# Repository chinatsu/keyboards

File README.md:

# keyboards

silly keyboard experiments

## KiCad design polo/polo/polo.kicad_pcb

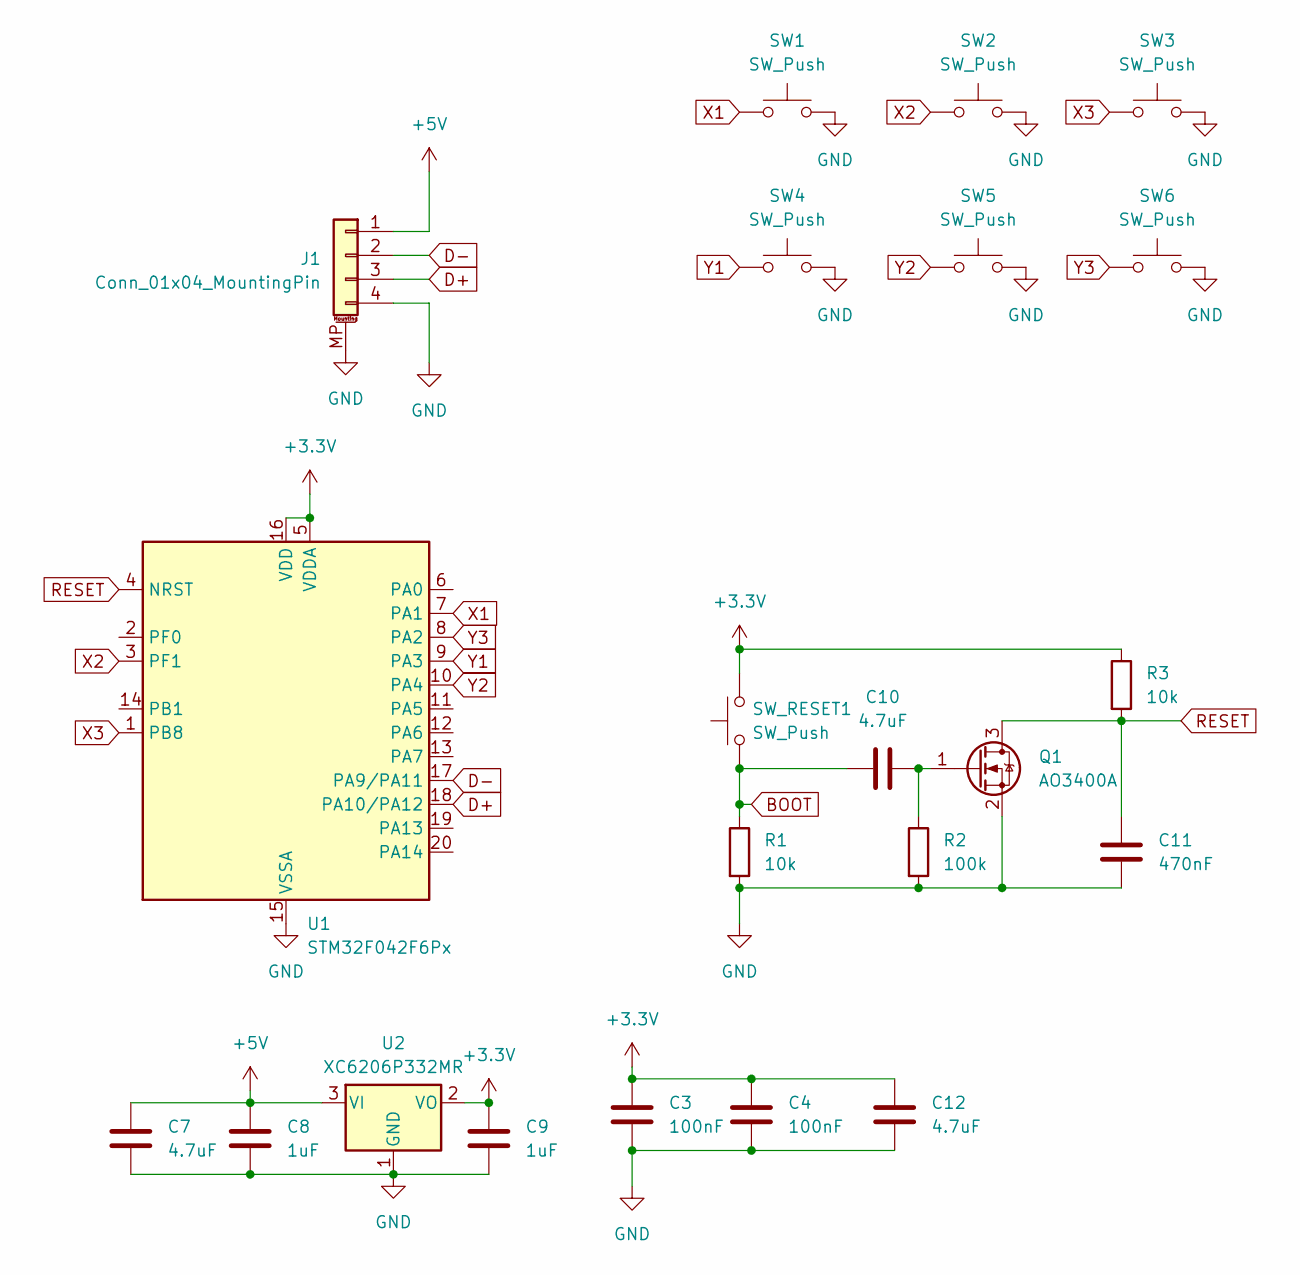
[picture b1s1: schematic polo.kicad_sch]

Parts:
C3, C4: 100nF; C_0805_2012Metric
C7, C10, C12: 4.7uF; C_0805_2012Metric
C8, C9: 1uF; C_0805_2012Metric
C11: 470nF; C_0805_2012Metric
J1: Conn_01x04_MountingPin; JST_SH_SM04B-SRSS-TB_1x04-1MP_P1.00mm_Horizontal
Q1: AO3400A; SOT-23
R1, R3: 10k; R_0805_2012Metric
R2: 100k; R_0805_2012Metric
SW1, SW2, SW3, SW4, SW5, SW6: SW_Push; SW_Cherry_MX_1.00u_PCB
SW_RESET1: SW_Push; SW_PUSH_1P1T_6x3.5mm_H4.3_APEM_MJTP1243
U1: STM32F042F6Px; TSSOP-20_4.4x6.5mm_P0.65mm
U2: XC6206P332MR; SOT-23-3

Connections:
+3.3V: C3.1, C4.1, C9.1, C12.1, R3.1, SW_RESET1.2, U1.5 (VDDA), U1.16 (VDD), U2.2 (VO)
+5V: C7.1, C8.1, J1.1, U2.3 (VI)
BOOT: C10.1, R1.1, SW_RESET1.1
D+: J1.3, U1.18 (PA10/PA12)
D-: J1.2, U1.17 (PA9/PA11)
GND: C3.2, C4.2, C7.2, C8.2, C9.2, C11.2, C12.2, J1.4, J1.MP (MountPin), Q1.2 (S), R1.2, R2.2, SW1.2, SW2.2, SW3.2, SW4.2, SW5.2, SW6.2, U1.15 (VSSA), U2.1 (GND)
unnamed: C10.2, Q1.1 (G), R2.1
RESET: C11.1, Q1.3 (D), R3.2, U1.4 (NRST)
X1: SW1.1, U1.7 (PA1)
X2: SW2.1, U1.3 (PF1)
X3: SW3.1, U1.1 (PB8)
Y1: SW4.1, U1.9 (PA3)
Y2: SW5.1, U1.10 (PA4)
Y3: SW6.1, U1.8 (PA2)

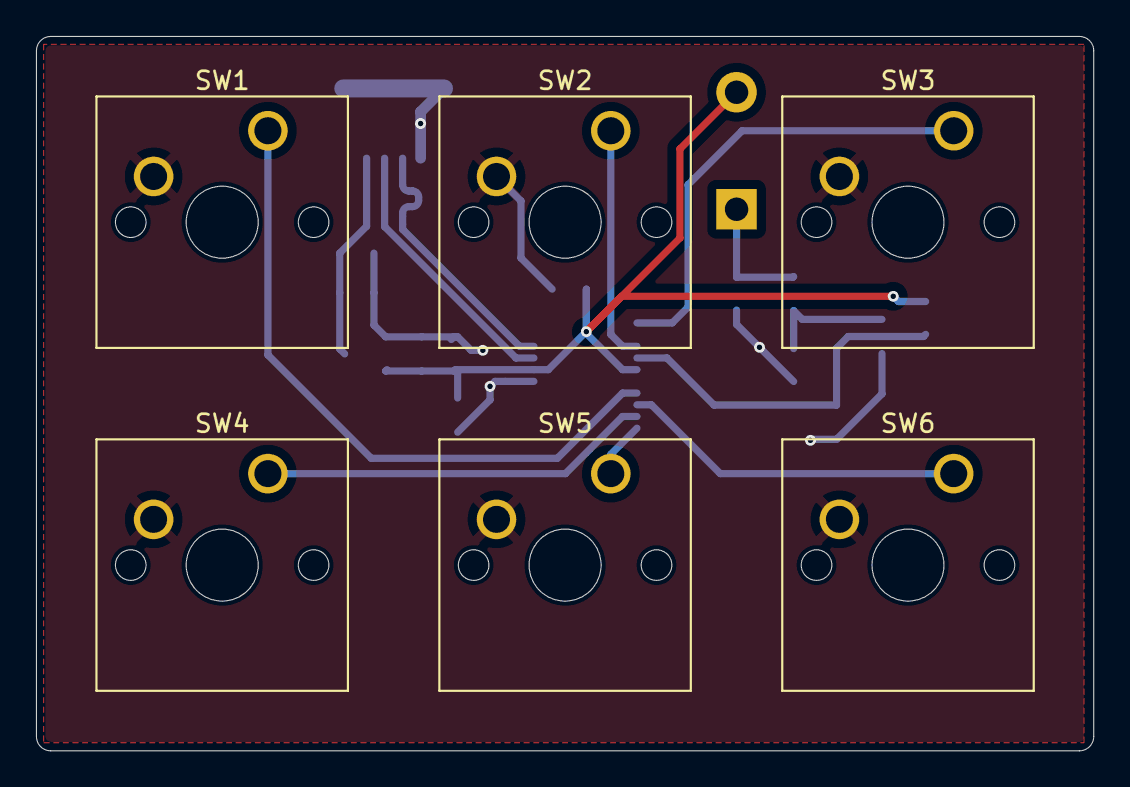
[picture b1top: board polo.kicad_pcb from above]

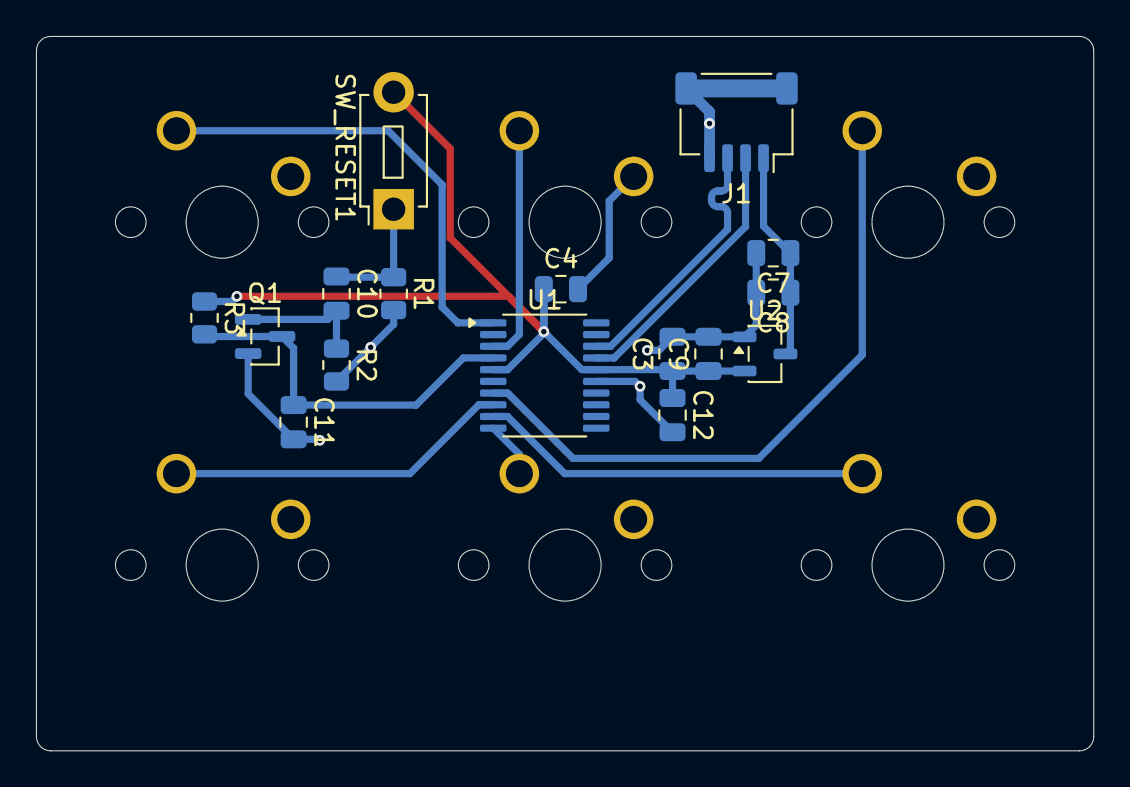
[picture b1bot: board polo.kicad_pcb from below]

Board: 2 copper layers, 58.7 x 39.7 mm, 22 parts (16 on the bottom side), 14 nets.

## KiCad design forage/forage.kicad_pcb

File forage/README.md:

# forage

my first attempt at a keyboard not using a pro micro or similar... let's see how it goes

## features

- 48 keys
- winkeyless
- arrow cluster
- uses unified daughterboard (s1, probably)

## layout

[keyboard-layout-editor](http://www.keyboard-layout-editor.com/#/gists/264eb9b4cfe87a9984ab72605ec59c53)

## plans

- design a case, maybe try to get a gasket mount style going?
- spend way too much money on a prototype cnc'd case
- be sad that things don't work, never work on this again

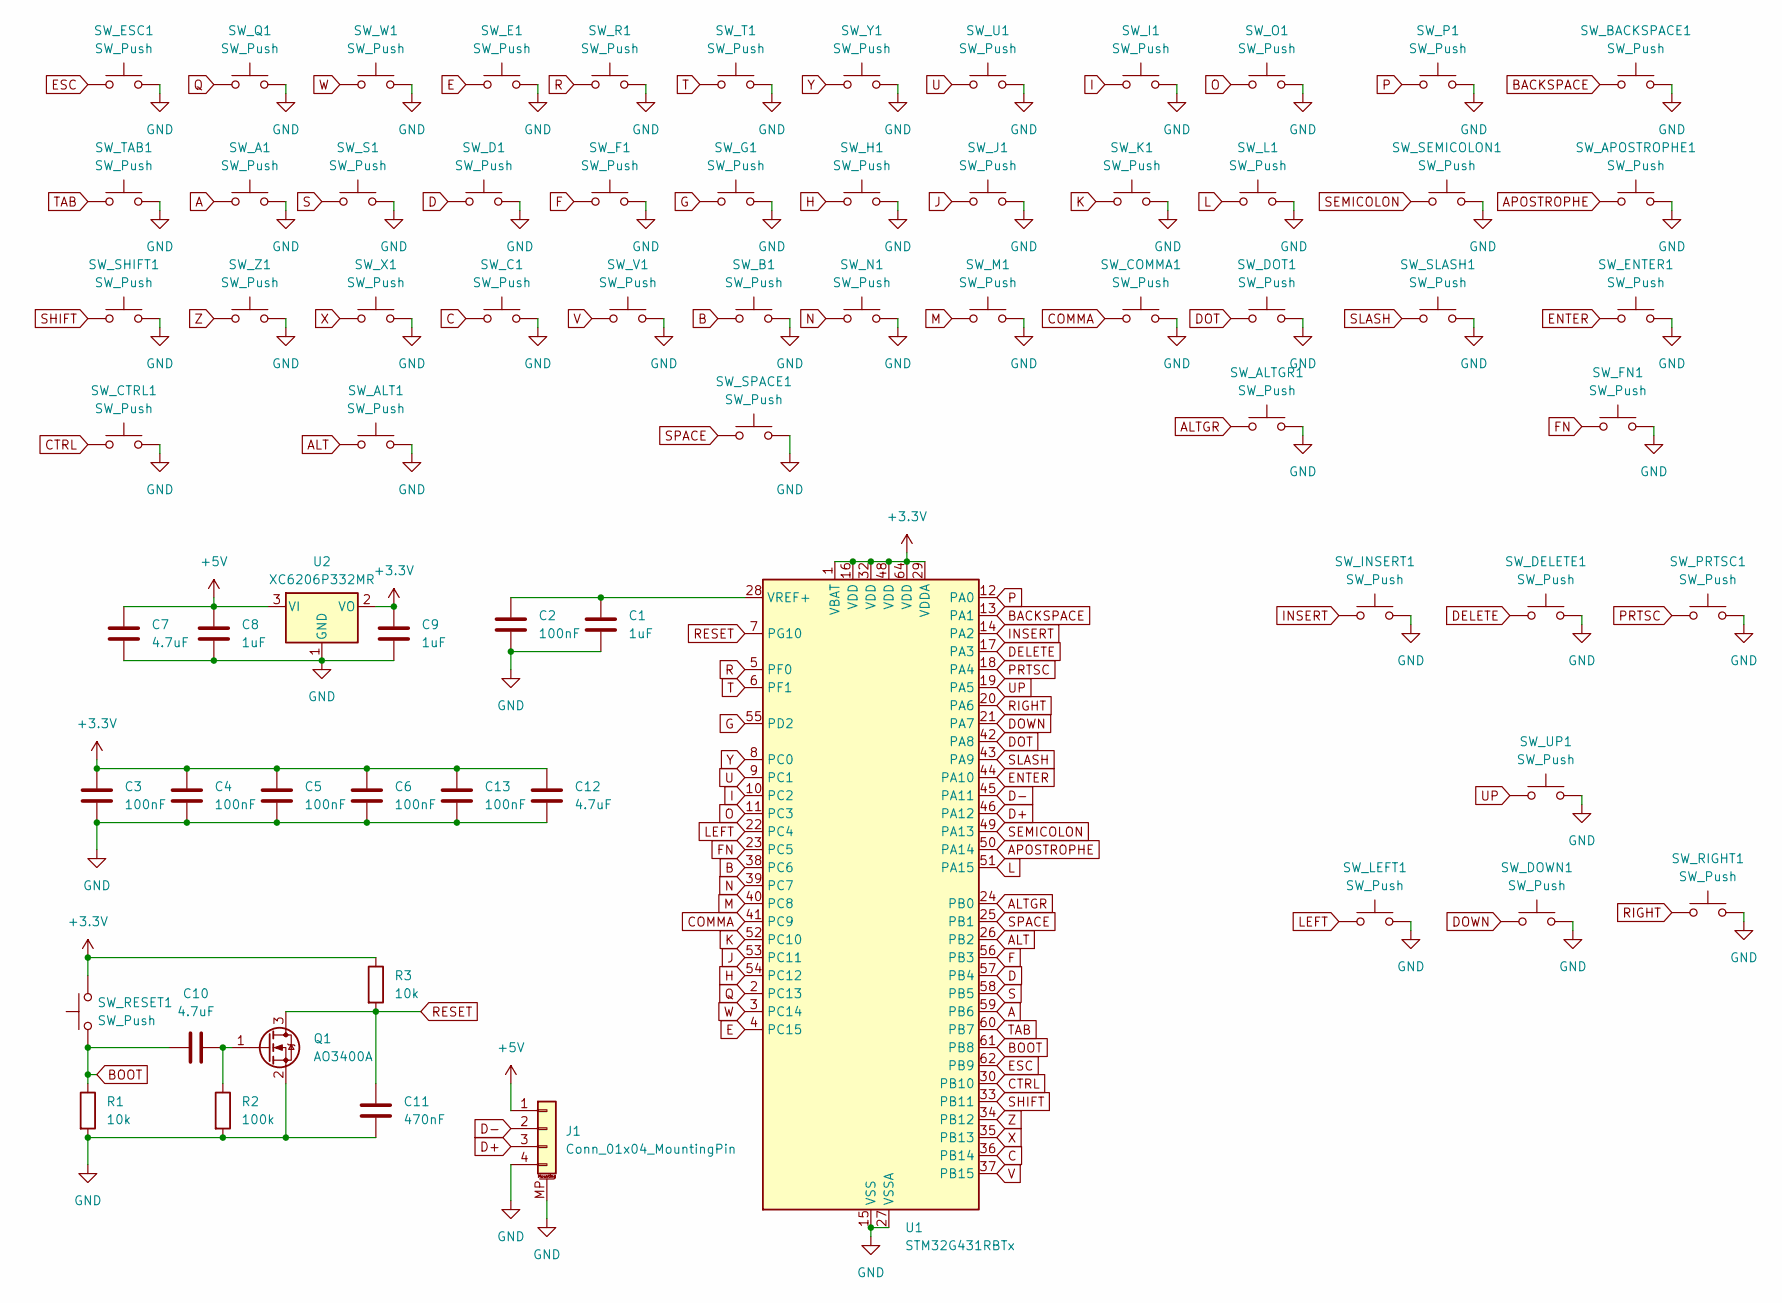
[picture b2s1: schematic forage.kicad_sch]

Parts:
C1, C8, C9: 1uF; C_0805_2012Metric
C2, C3, C4, C5, C6, C13: 100nF; C_0805_2012Metric
C7, C10, C12: 4.7uF; C_0805_2012Metric
C11: 470nF; C_0805_2012Metric
J1: Conn_01x04_MountingPin; JST_SH_SM04B-SRSS-TB_1x04-1MP_P1.00mm_Horizontal
Q1: AO3400A; SOT-23
R1, R3: 10k; R_0805_2012Metric
R2: 100k; R_0805_2012Metric
SW_A1: SW_Push; SW_Cherry_MX_1.00u_PCB
SW_ALT1: SW_Push; SW_Cherry_MX_1.00u_PCB
SW_ALTGR1: SW_Push; SW_Cherry_MX_1.25u_PCB
SW_APOSTROPHE1: SW_Push; SW_Cherry_MX_1.50u_PCB
SW_B1: SW_Push; SW_Cherry_MX_1.00u_PCB
SW_BACKSPACE1: SW_Push; SW_Cherry_MX_1.75u_PCB
SW_C1: SW_Push; SW_Cherry_MX_1.00u_PCB
SW_COMMA1: SW_Push; SW_Cherry_MX_1.00u_PCB
SW_CTRL1: SW_Push; SW_Cherry_MX_1.25u_PCB
SW_D1: SW_Push; SW_Cherry_MX_1.00u_PCB
SW_DELETE1: SW_Push; SW_Cherry_MX_1.00u_PCB
SW_DOT1: SW_Push; SW_Cherry_MX_1.00u_PCB
SW_DOWN1: SW_Push; SW_Cherry_MX_1.00u_PCB
SW_E1: SW_Push; SW_Cherry_MX_1.00u_PCB
SW_ENTER1: SW_Push; SW_Cherry_MX_1.25u_PCB
SW_ESC1: SW_Push; SW_Cherry_MX_1.00u_PCB
SW_F1: SW_Push; SW_Cherry_MX_1.00u_PCB
SW_FN1: SW_Push; SW_Cherry_MX_1.00u_PCB
SW_G1: SW_Push; SW_Cherry_MX_1.00u_PCB
SW_H1: SW_Push; SW_Cherry_MX_1.00u_PCB
SW_I1: SW_Push; SW_Cherry_MX_1.00u_PCB
SW_INSERT1: SW_Push; SW_Cherry_MX_1.00u_PCB
SW_J1: SW_Push; SW_Cherry_MX_1.00u_PCB
SW_K1: SW_Push; SW_Cherry_MX_1.00u_PCB
SW_L1: SW_Push; SW_Cherry_MX_1.00u_PCB
SW_LEFT1: SW_Push; SW_Cherry_MX_1.00u_PCB
SW_M1: SW_Push; SW_Cherry_MX_1.00u_PCB
SW_N1: SW_Push; SW_Cherry_MX_1.00u_PCB
SW_O1: SW_Push; SW_Cherry_MX_1.00u_PCB
SW_P1: SW_Push; SW_Cherry_MX_1.00u_PCB
SW_PRTSC1: SW_Push; SW_Cherry_MX_1.00u_PCB
SW_Q1: SW_Push; SW_Cherry_MX_1.00u_PCB
SW_R1: SW_Push; SW_Cherry_MX_1.00u_PCB
SW_RESET1: SW_Push; SW_PUSH_1P1T_6x3.5mm_H4.3_APEM_MJTP1243
SW_RIGHT1: SW_Push; SW_Cherry_MX_1.00u_PCB
SW_S1: SW_Push; SW_Cherry_MX_1.00u_PCB
SW_SEMICOLON1: SW_Push; SW_Cherry_MX_1.00u_PCB
SW_SHIFT1: SW_Push; SW_Cherry_MX_1.50u_PCB
SW_SLASH1: SW_Push; SW_Cherry_MX_1.00u_PCB
SW_SPACE1: SW_Push; SW_Cherry_MX_6.25u_PCB
SW_T1: SW_Push; SW_Cherry_MX_1.00u_PCB
SW_TAB1: SW_Push; SW_Cherry_MX_1.25u_PCB
SW_U1: SW_Push; SW_Cherry_MX_1.00u_PCB
SW_UP1: SW_Push; SW_Cherry_MX_1.00u_PCB
SW_V1: SW_Push; SW_Cherry_MX_1.00u_PCB
SW_W1: SW_Push; SW_Cherry_MX_1.00u_PCB
SW_X1: SW_Push; SW_Cherry_MX_1.00u_PCB
SW_Y1: SW_Push; SW_Cherry_MX_1.00u_PCB
SW_Z1: SW_Push; SW_Cherry_MX_1.00u_PCB
U1: STM32G431RBTx; LQFP-64_10x10mm_P0.5mm
U2: XC6206P332MR; SOT-23-3

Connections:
+3.3V: C3.1, C4.1, C5.1, C6.1, C9.1, C12.1, C13.1, R3.1, SW_RESET1.2, U1.1 (VBAT), U1.16 (VDD), U1.29 (VDDA), U1.32 (VDD), U1.48 (VDD), U1.64 (VDD), U2.2 (VO)
+5V: C7.1, C8.1, J1.1, U2.3 (VI)
A: SW_A1.1, U1.59 (PB6)
ALT: SW_ALT1.1, U1.26 (PB2)
ALTGR: SW_ALTGR1.1, U1.24 (PB0)
APOSTROPHE: SW_APOSTROPHE1.1, U1.50 (PA14)
B: SW_B1.1, U1.38 (PC6)
BACKSPACE: SW_BACKSPACE1.1, U1.13 (PA1)
BOOT: C10.1, R1.1, SW_RESET1.1, U1.61 (PB8)
C: SW_C1.1, U1.36 (PB14)
COMMA: SW_COMMA1.1, U1.41 (PC9)
CTRL: SW_CTRL1.1, U1.30 (PB10)
D: SW_D1.1, U1.57 (PB4)
D+: J1.3, U1.46 (PA12)
D-: J1.2, U1.45 (PA11)
DELETE: SW_DELETE1.1, U1.17 (PA3)
DOT: SW_DOT1.1, U1.42 (PA8)
DOWN: SW_DOWN1.1, U1.21 (PA7)
E: SW_E1.1, U1.4 (PC15)
ENTER: SW_ENTER1.1, U1.44 (PA10)
ESC: SW_ESC1.1, U1.62 (PB9)
F: SW_F1.1, U1.56 (PB3)
FN: SW_FN1.1, U1.23 (PC5)
G: SW_G1.1, U1.55 (PD2)
GND: C1.2, C2.2, C3.2, C4.2, C5.2, C6.2, C7.2, C8.2, C9.2, C11.2, C12.2, C13.2, J1.4, J1.MP (MountPin), Q1.2 (S), R1.2, R2.2, SW_A1.2, SW_ALT1.2, SW_ALTGR1.2, SW_APOSTROPHE1.2, SW_B1.2, SW_BACKSPACE1.2, SW_C1.2, SW_COMMA1.2, SW_CTRL1.2, SW_D1.2, SW_DELETE1.2, SW_DOT1.2, SW_DOWN1.2, SW_E1.2, SW_ENTER1.2, SW_ESC1.2, SW_F1.2, SW_FN1.2, SW_G1.2, SW_H1.2, SW_I1.2, SW_INSERT1.2, SW_J1.2, SW_K1.2, SW_L1.2, SW_LEFT1.2, SW_M1.2, SW_N1.2, SW_O1.2, SW_P1.2, SW_PRTSC1.2, SW_Q1.2, SW_R1.2, SW_RIGHT1.2, SW_S1.2, SW_SEMICOLON1.2, SW_SHIFT1.2, SW_SLASH1.2, SW_SPACE1.2, SW_T1.2, SW_TAB1.2, SW_U1.2, SW_UP1.2, SW_V1.2, SW_W1.2, SW_X1.2, SW_Y1.2, SW_Z1.2, U1.15 (VSS), U1.27 (VSSA), U1.31 (VSS), U1.47 (VSS), U1.63 (VSS), U2.1 (GND)
H: SW_H1.1, U1.54 (PC12)
I: SW_I1.1, U1.10 (PC2)
INSERT: SW_INSERT1.1, U1.14 (PA2)
J: SW_J1.1, U1.53 (PC11)
K: SW_K1.1, U1.52 (PC10)
L: SW_L1.1, U1.51 (PA15)
LEFT: SW_LEFT1.1, U1.22 (PC4)
M: SW_M1.1, U1.40 (PC8)
N: SW_N1.1, U1.39 (PC7)
unnamed: C10.2, Q1.1 (G), R2.1
unnamed: C1.1, C2.1, U1.28 (VREF+)
O: SW_O1.1, U1.11 (PC3)
P: SW_P1.1, U1.12 (PA0)
PRTSC: SW_PRTSC1.1, U1.18 (PA4)
Q: SW_Q1.1, U1.2 (PC13)
R: SW_R1.1, U1.5 (PF0)
RESET: C11.1, Q1.3 (D), R3.2, U1.7 (PG10)
RIGHT: SW_RIGHT1.1, U1.20 (PA6)
S: SW_S1.1, U1.58 (PB5)
SEMICOLON: SW_SEMICOLON1.1, U1.49 (PA13)
SHIFT: SW_SHIFT1.1, U1.33 (PB11)
SLASH: SW_SLASH1.1, U1.43 (PA9)
SPACE: SW_SPACE1.1, U1.25 (PB1)
T: SW_T1.1, U1.6 (PF1)
TAB: SW_TAB1.1, U1.60 (PB7)
U: SW_U1.1, U1.9 (PC1)
UP: SW_UP1.1, U1.19 (PA5)
V: SW_V1.1, U1.37 (PB15)
W: SW_W1.1, U1.3 (PC14)
X: SW_X1.1, U1.35 (PB13)
Y: SW_Y1.1, U1.8 (PC0)
Z: SW_Z1.1, U1.34 (PB12)

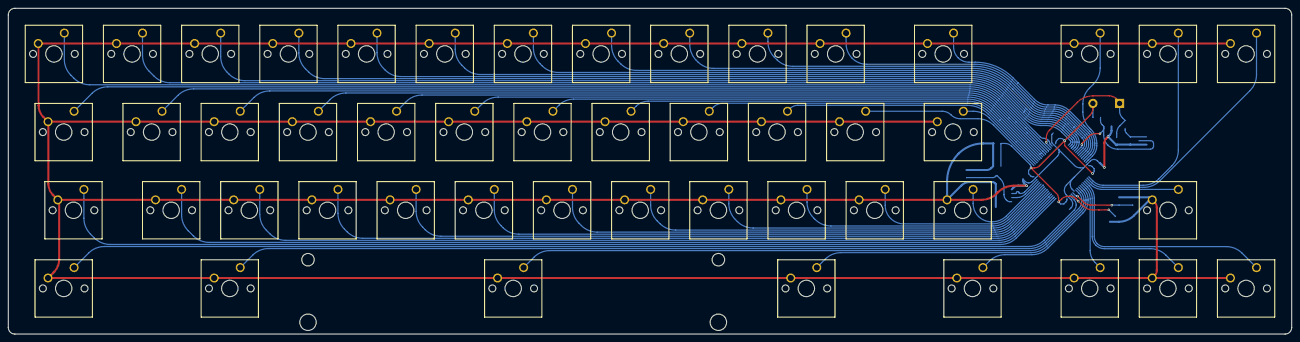
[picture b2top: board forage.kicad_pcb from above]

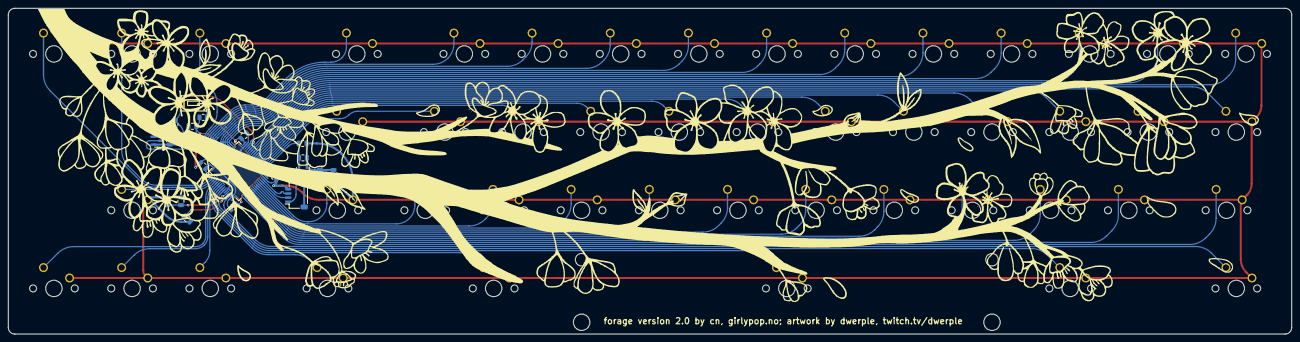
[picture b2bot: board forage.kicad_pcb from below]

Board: 2 copper layers, 312.7 x 79.4 mm, 69 parts (21 on the bottom side), 57 nets.

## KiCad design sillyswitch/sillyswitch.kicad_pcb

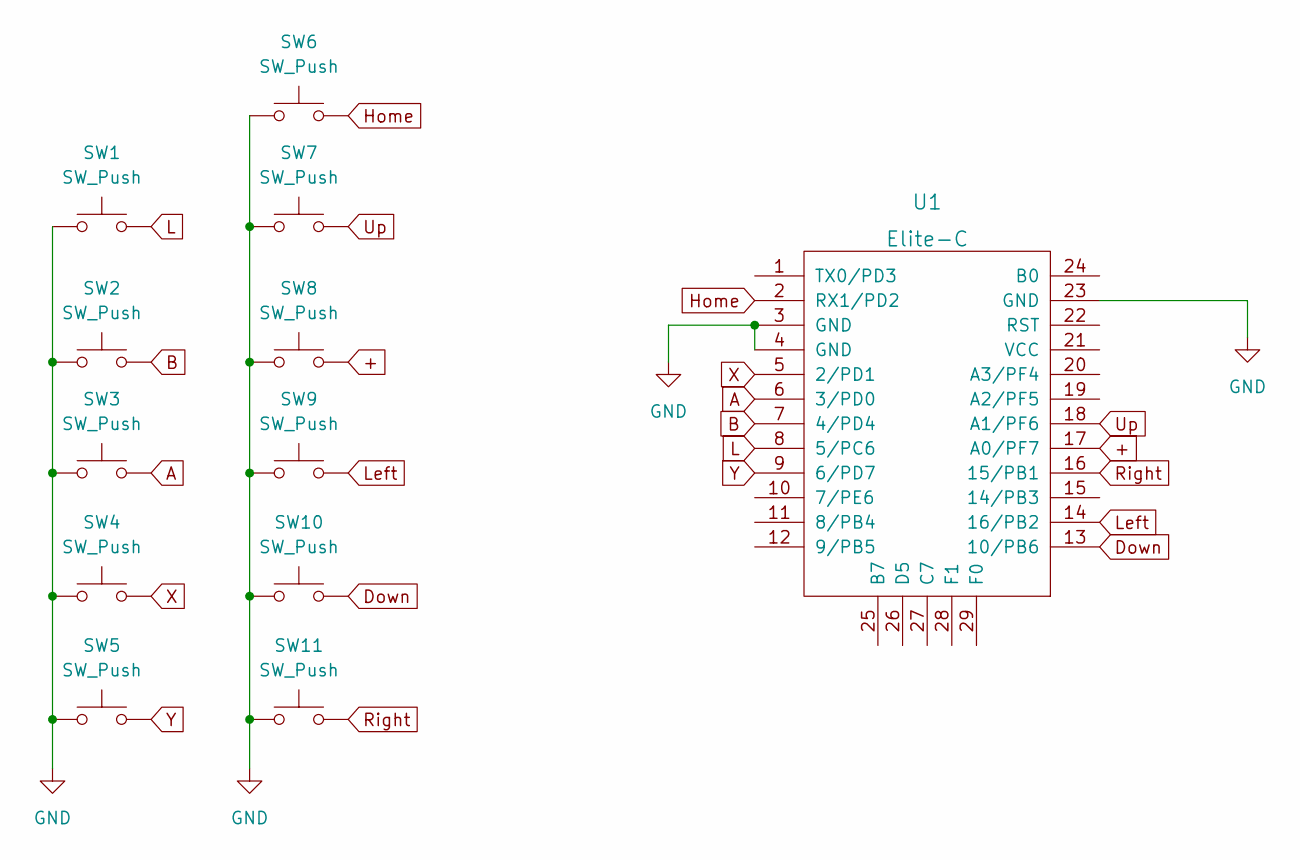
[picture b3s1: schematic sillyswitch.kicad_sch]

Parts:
SW1: SW_Push; SW_Cherry_MX_1.50u_PCB
SW2, SW3, SW4, SW6, SW7, SW8, SW9, SW10, SW11: SW_Push; SW_Cherry_MX_1.00u_PCB
SW5: SW_Push; SW_Cherry_MX_2.00u_PCB
U1: Elite-C

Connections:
+: SW8.2, U1.17 (A0/PF7)
A: SW3.2, U1.6 (3/PD0)
B: SW2.2, U1.7 (4/PD4)
Down: SW10.2, U1.13 (10/PB6)
GND: SW1.1, SW2.1, SW3.1, SW4.1, SW5.1, SW6.1, SW7.1, SW8.1, SW9.1, SW10.1, SW11.1, U1.3 (GND), U1.4 (GND), U1.23 (GND)
Home: SW6.2, U1.2 (RX1/PD2)
L: SW1.2, U1.8 (5/PC6)
Left: SW9.2, U1.14 (16/PB2)
Right: SW11.2, U1.16 (15/PB1)
Up: SW7.2, U1.18 (A1/PF6)
X: SW4.2, U1.5 (2/PD1)
Y: SW5.2, U1.9 (6/PD7)

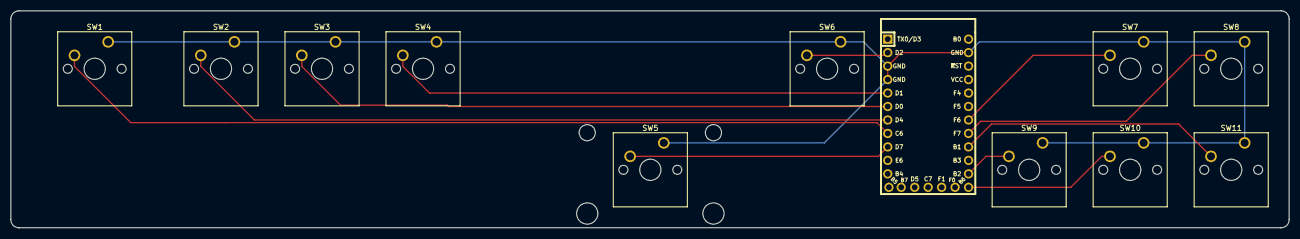
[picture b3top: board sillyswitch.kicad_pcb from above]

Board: 2 copper layers, 241.0 x 40.9 mm, 12 parts (0 on the bottom side), 12 nets.

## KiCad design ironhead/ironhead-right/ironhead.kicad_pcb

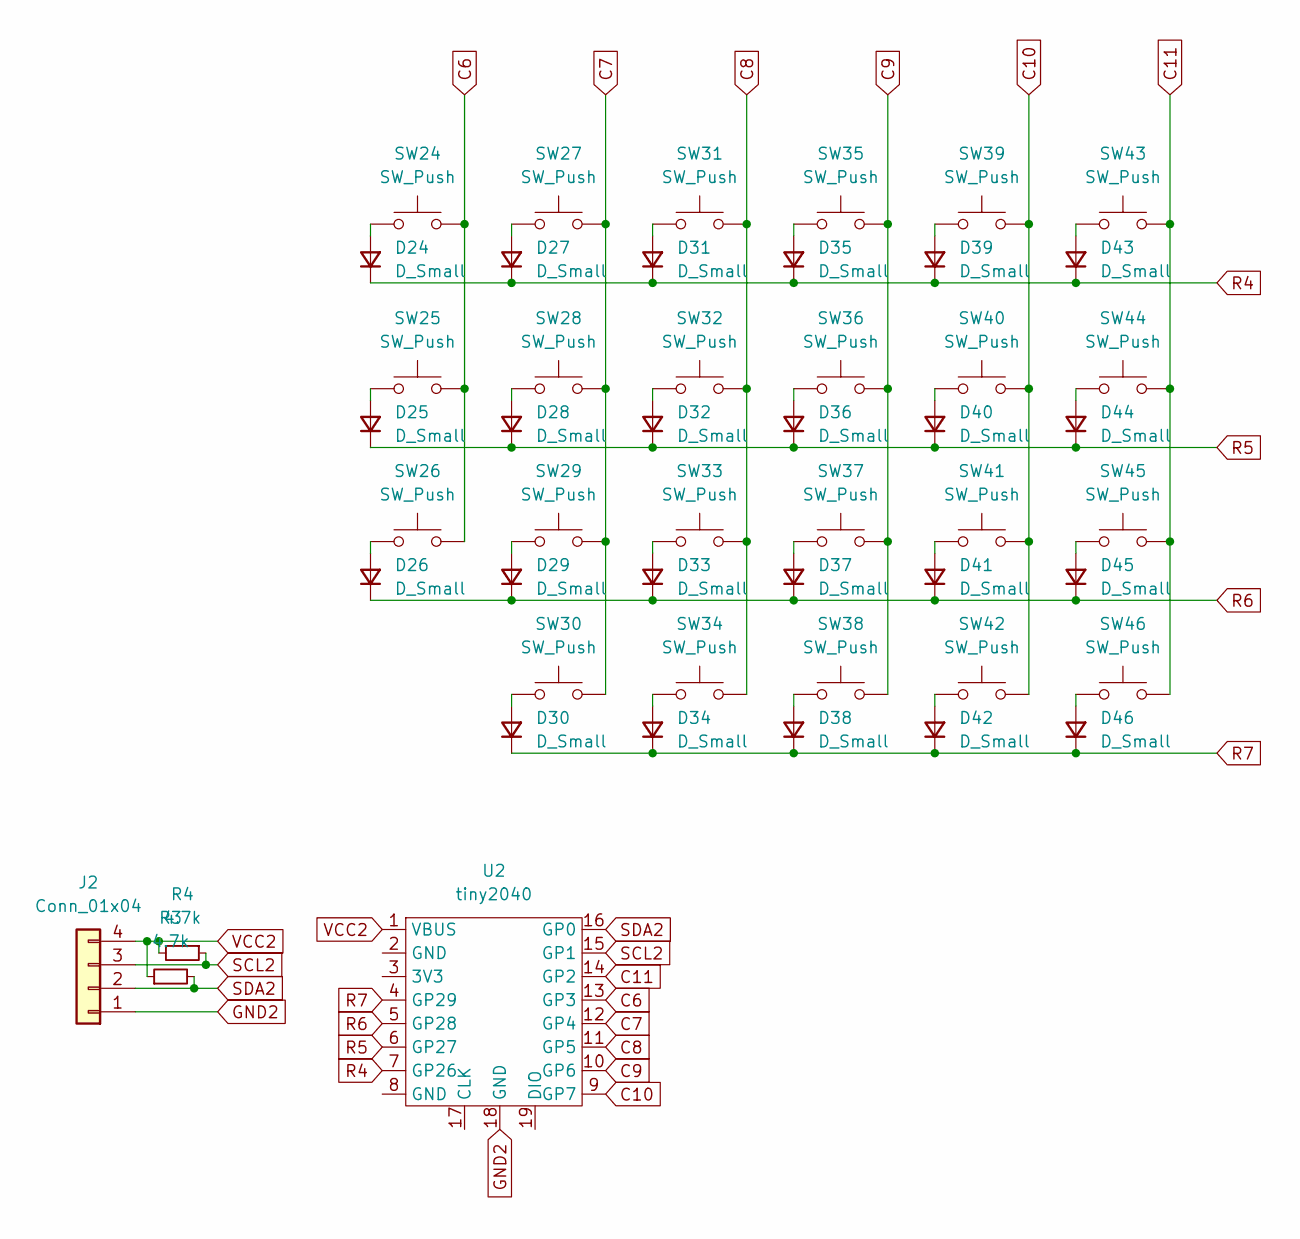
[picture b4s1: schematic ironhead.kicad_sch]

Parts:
D24, D25, D26, D27, D28, D29, D30, D31, D32, D33, D34, D35, D36, D37, D38, D39, D40, D41, D42, D43, D44, D45, D46: D_Small; D_SOD-123
J2: Conn_01x04; Molex_Sabre_43160-1104_1x04_P7.49mm_Horizontal
R3, R4: 4.7k; R_0805_2012Metric
SW24, SW25, SW26, SW27, SW28, SW29, SW30, SW31, SW32, SW33, SW34, SW35, SW36, SW37, SW38, SW39, SW40, SW41, SW42, SW43, SW44, SW45, SW46: SW_Push; SW_Cherry_MX_1.00u_PCB
U2: tiny2040

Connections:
C6: SW24.2, SW25.2, SW26.2, U2.13 (GP3)
C7: SW27.2, SW28.2, SW29.2, SW30.2, U2.12 (GP4)
C8: SW31.2, SW32.2, SW33.2, SW34.2, U2.11 (GP5)
C9: SW35.2, SW36.2, SW37.2, SW38.2, U2.10 (GP6)
C10: SW39.2, SW40.2, SW41.2, SW42.2, U2.9 (GP7)
C11: SW43.2, SW44.2, SW45.2, SW46.2, U2.14 (GP2)
GND2: J2.1, U2.18 (GND)
unnamed: D24.2 (A), SW24.1
unnamed: D25.2 (A), SW25.1
unnamed: D26.2 (A), SW26.1
unnamed: D27.2 (A), SW27.1
unnamed: D28.2 (A), SW28.1
unnamed: D29.2 (A), SW29.1
unnamed: D30.2 (A), SW30.1
unnamed: D31.2 (A), SW31.1
unnamed: D32.2 (A), SW32.1
unnamed: D33.2 (A), SW33.1
unnamed: D34.2 (A), SW34.1
unnamed: D35.2 (A), SW35.1
unnamed: D36.2 (A), SW36.1
unnamed: D37.2 (A), SW37.1
unnamed: D38.2 (A), SW38.1
unnamed: D39.2 (A), SW39.1
unnamed: D40.2 (A), SW40.1
unnamed: D41.2 (A), SW41.1
unnamed: D42.2 (A), SW42.1
unnamed: D43.2 (A), SW43.1
unnamed: D44.2 (A), SW44.1
unnamed: D45.2 (A), SW45.1
unnamed: D46.2 (A), SW46.1
R4: D24.1 (K), D27.1 (K), D31.1 (K), D35.1 (K), D39.1 (K), D43.1 (K), U2.7 (GP26)
R5: D25.1 (K), D28.1 (K), D32.1 (K), D36.1 (K), D40.1 (K), D44.1 (K), U2.6 (GP27)
R6: D26.1 (K), D29.1 (K), D33.1 (K), D37.1 (K), D41.1 (K), D45.1 (K), U2.5 (GP28)
R7: D30.1 (K), D34.1 (K), D38.1 (K), D42.1 (K), D46.1 (K), U2.4 (GP29)
SCL2: J2.3, R4.1, U2.15 (GP1)
SDA2: J2.2, R3.2, U2.16 (GP0)
VCC2: J2.4, R3.1, R4.2, U2.1 (VBUS)

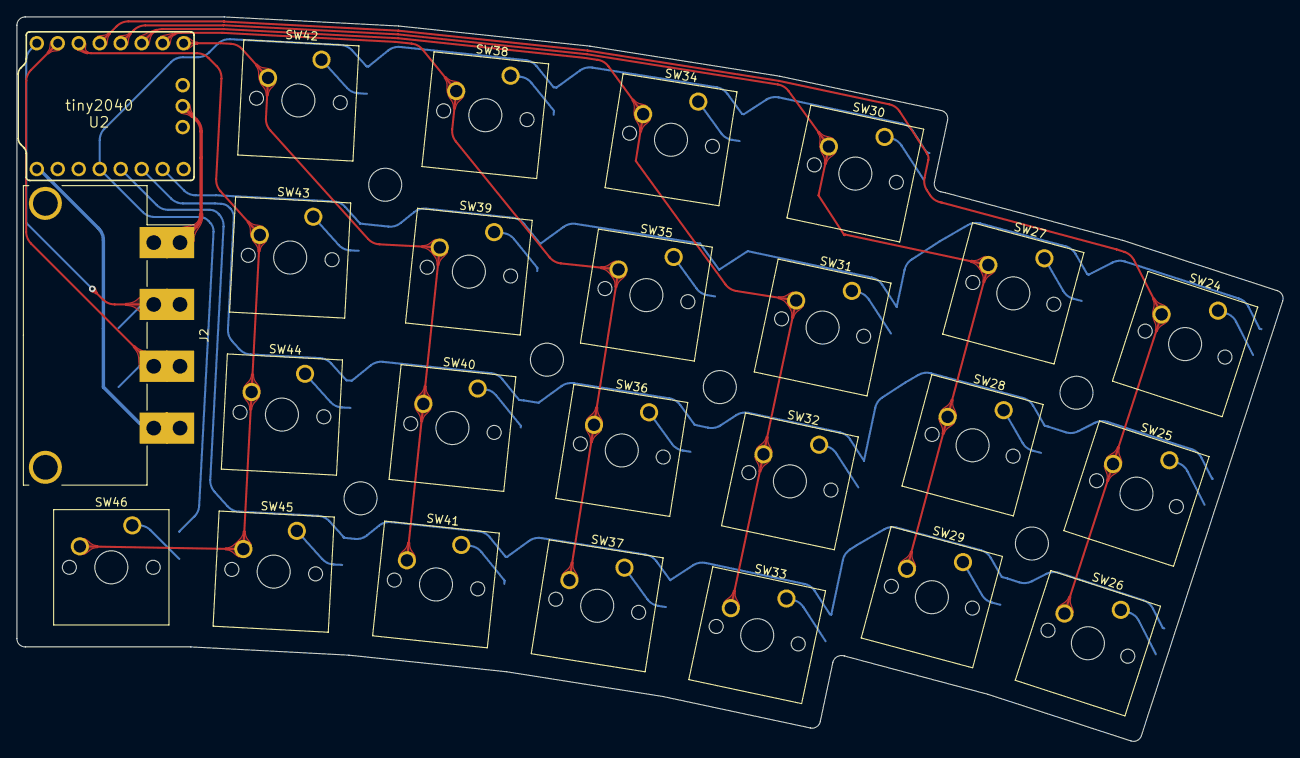
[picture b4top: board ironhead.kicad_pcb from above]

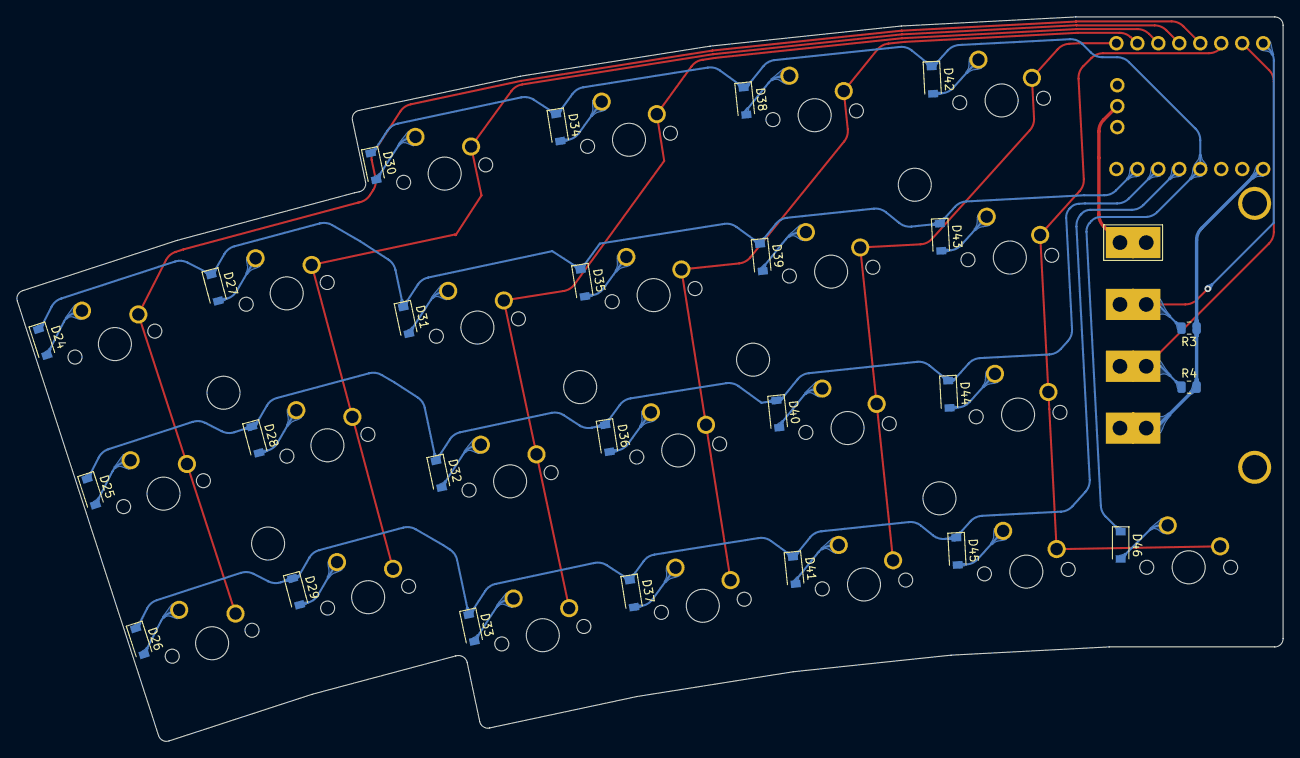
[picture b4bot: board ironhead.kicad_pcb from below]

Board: 2 copper layers, 153.4 x 87.7 mm, 50 parts (25 on the bottom side), 37 nets.

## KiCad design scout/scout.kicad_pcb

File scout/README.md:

# scout

alpha keys, some arrows and an enter key. what more could you need?

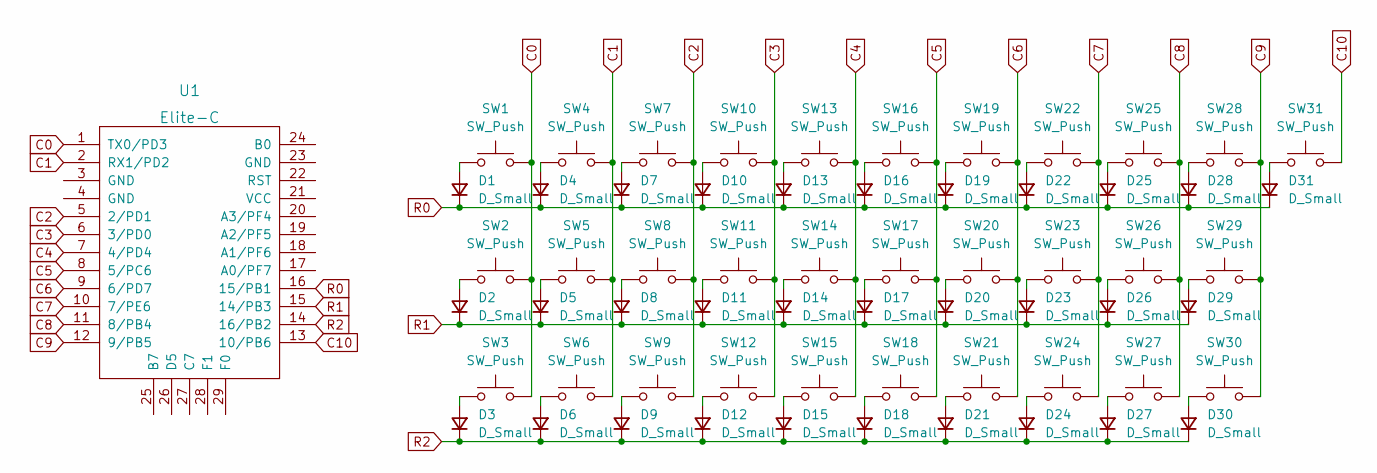
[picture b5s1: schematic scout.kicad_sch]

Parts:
D1, D2, D3, D4, D5, D6, D7, D8, D9, D10, D11, D12, D13, D14, D15, D16, D17, D18, D19, D20, D21, D22, D23, D24, D25, D26, D27, D28, D29, D30, D31: D_Small; D_SOD-123
SW1, SW2, SW3, SW4, SW5, SW6, SW7, SW8, SW9, SW10, SW11, SW12, SW13, SW14, SW15, SW16, SW17, SW18, SW19, SW20, SW21, SW22, SW23, SW24, SW25, SW26, SW27, SW28, SW29, SW30: SW_Push; SW_Cherry_MX_1.00u_PCB
SW31: SW_Push; SW_Cherry_MX_ISOEnter_PCB
U1: Elite-C

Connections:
C0: SW1.2, SW2.2, SW3.2, U1.1 (TX0/PD3)
C1: SW4.2, SW5.2, SW6.2, U1.2 (RX1/PD2)
C2: SW7.2, SW8.2, SW9.2, U1.5 (2/PD1)
C3: SW10.2, SW11.2, SW12.2, U1.6 (3/PD0)
C4: SW13.2, SW14.2, SW15.2, U1.7 (4/PD4)
C5: SW16.2, SW17.2, SW18.2, U1.8 (5/PC6)
C6: SW19.2, SW20.2, SW21.2, U1.9 (6/PD7)
C7: SW22.2, SW23.2, SW24.2, U1.10 (7/PE6)
C8: SW25.2, SW26.2, SW27.2, U1.11 (8/PB4)
C9: SW28.2, SW29.2, SW30.2, U1.12 (9/PB5)
C10: SW31.2, U1.13 (10/PB6)
unnamed: D1.2 (A), SW1.1
unnamed: D2.2 (A), SW2.1
unnamed: D3.2 (A), SW3.1
unnamed: D4.2 (A), SW4.1
unnamed: D5.2 (A), SW5.1
unnamed: D6.2 (A), SW6.1
unnamed: D7.2 (A), SW7.1
unnamed: D8.2 (A), SW8.1
unnamed: D9.2 (A), SW9.1
unnamed: D10.2 (A), SW10.1
unnamed: D11.2 (A), SW11.1
unnamed: D12.2 (A), SW12.1
unnamed: D13.2 (A), SW13.1
unnamed: D14.2 (A), SW14.1
unnamed: D15.2 (A), SW15.1
unnamed: D16.2 (A), SW16.1
unnamed: D17.2 (A), SW17.1
unnamed: D18.2 (A), SW18.1
unnamed: D19.2 (A), SW19.1
unnamed: D20.2 (A), SW20.1
unnamed: D21.2 (A), SW21.1
unnamed: D22.2 (A), SW22.1
unnamed: D23.2 (A), SW23.1
unnamed: D24.2 (A), SW24.1
unnamed: D25.2 (A), SW25.1
unnamed: D26.2 (A), SW26.1
unnamed: D27.2 (A), SW27.1
unnamed: D28.2 (A), SW28.1
unnamed: D29.2 (A), SW29.1
unnamed: D30.2 (A), SW30.1
unnamed: D31.2 (A), SW31.1
R0: D1.1 (K), D4.1 (K), D7.1 (K), D10.1 (K), D13.1 (K), D16.1 (K), D19.1 (K), D22.1 (K), D25.1 (K), D28.1 (K), D31.1 (K), U1.16 (15/PB1)
R1: D2.1 (K), D5.1 (K), D8.1 (K), D11.1 (K), D14.1 (K), D17.1 (K), D20.1 (K), D23.1 (K), D26.1 (K), D29.1 (K), U1.15 (14/PB3)
R2: D3.1 (K), D6.1 (K), D9.1 (K), D12.1 (K), D15.1 (K), D18.1 (K), D21.1 (K), D24.1 (K), D27.1 (K), D30.1 (K), U1.14 (16/PB2)

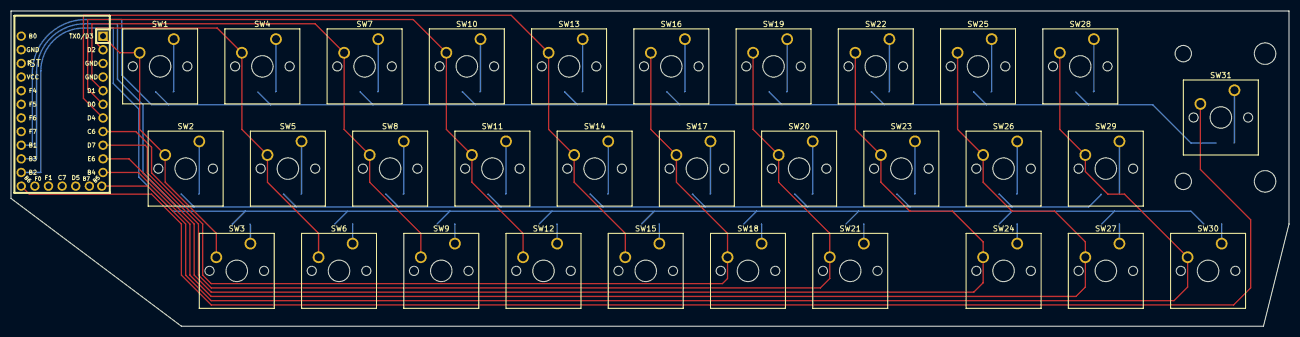
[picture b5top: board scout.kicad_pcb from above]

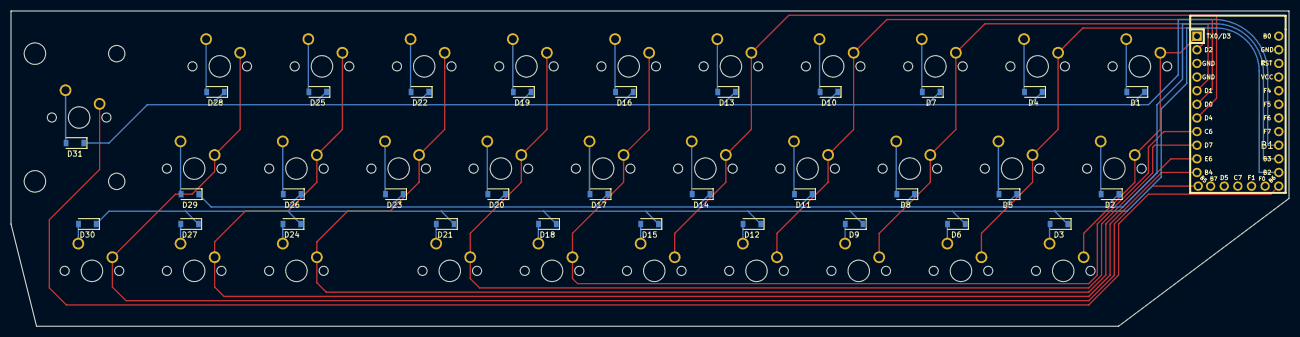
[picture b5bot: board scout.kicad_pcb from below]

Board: 2 copper layers, 238.1 x 58.7 mm, 63 parts (32 on the bottom side), 45 nets.

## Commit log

2022-02-08 create kicad project
2022-02-08 add submodules
2022-02-08 add lib tables
2022-02-08 add keebio submodule
2022-02-08 add lib tables for keebio components
2022-02-08 sort out submodules and kicad tables
2022-02-08 start work on mcu stuff
2022-02-08 set up switch grid, drop reset switch and caps
2022-02-08 assign footprints
2022-02-08 start work on placing footprints
2022-02-08 place diodes
2022-02-08 draw the rest of the owl?
2022-02-08 use non-hotswap footprints, also i made this backwards
2022-02-09 retrace, reorient, and all that
2022-02-09 retrace front
2022-02-09 some small things before production order
2022-02-12 fix a footprint
2022-02-12 remove outdated gerber files
2022-02-12 add a little description
2022-02-22 rename keyboard
2022-02-22 readd submodules
2022-02-22 add link to qmk
2022-02-23 scout
2022-06-17 add ironhead i guess
2023-06-07 upload sillyswitch
2024-04-28 wip: forage
2024-04-28 move connector so D+/D- has a direct path
2024-04-28 move caps around a little bit to reduce vias
2024-04-28 finalize stuff??? who knows
2024-04-28 add readme
2024-05-08 wip: v2
2024-05-08 fix connector pins.... i think!
2024-05-08 make the traces round too
2024-05-09 move some ground traces to the other side
2024-05-09 add a license
2024-05-15 switch to jst
2024-05-15 round a trace a little more
2024-05-15 prepare a text area for attribution
2024-06-16 update silkscreen stuff
2024-06-16 correct xc6206 thingy
2024-06-16 fix some pesky drc errors, make vbat trace follow 3.3v on the front side
2024-06-16 connect vbat to the 3.3v net
2024-06-16 recommended schmeccomended??? ok
2024-07-20 wip: start work on moving the cluster 6 subunits to the right
2024-07-20 reestablish connections, todo: smooth tracks
2024-07-20 smooth the new tracks
2025-10-05 update: artwork
2025-10-31 lil macro pad
2025-11-05 update circuitboard with correct pin assignments lol
